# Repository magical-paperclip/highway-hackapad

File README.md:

# highway hackpad
pov: you make your first hardware project and with 12 channel pings in ur personal channel and 8 people helping you build a pcb.
im very proud of my determination and i kept going even when i wanted to give up.

### inspiration
my original inspiration was to build a hackpad that would help me copy and paste, delete, space and using f5 for dev tools as it would help me debug at a faster pace

### Specifications

bom:
4x cherry mx switches (blue)
2x SK6812 mini leds
1x XIAO rp2040
4x blank dsa keycaps (black)

others:
- kmk firmware
- top.step 
- bottom.step

### final product

### info:
the pcb will be secured to the case w double sided tape to prevent it from falling out

schematic            |  pcb         |   case
:-------------------------:|:-------------------------:|:-------------------------:|
    |    |

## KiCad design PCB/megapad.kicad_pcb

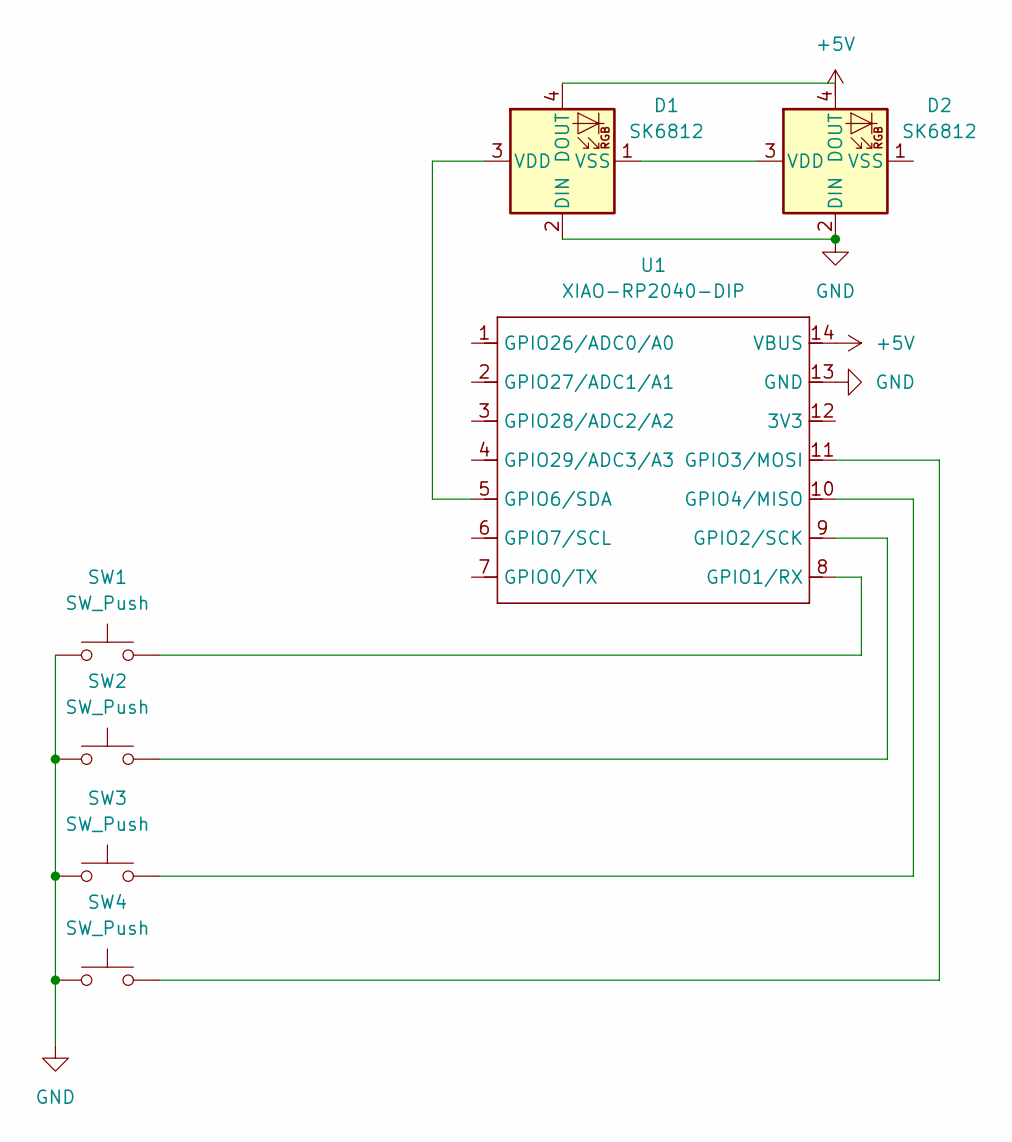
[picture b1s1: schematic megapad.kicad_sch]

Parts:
D1, D2: SK6812; LED_SK6812_PLCC4_5.0x5.0mm_P3.2mm
SW1, SW2, SW3, SW4: SW_Push; SW_Cherry_MX_1.00u_PCB
U1: XIAO-RP2040-DIP

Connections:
+5V: U1.14 (VBUS)
GND: D1.2 (DIN), D2.2 (DIN), SW1.1, SW2.1, SW3.1, SW4.1, U1.13 (GND)
unnamed: D1.4 (DOUT), D2.4 (DOUT)
unnamed: D1.3 (VDD), U1.5 (GPIO6/SDA)
unnamed: D1.1 (VSS), D2.3 (VDD)
unnamed: SW1.2, U1.8 (GPIO1/RX)
unnamed: SW2.2, U1.9 (GPIO2/SCK)
unnamed: SW4.2, U1.11 (GPIO3/MOSI)
unnamed: SW3.2, U1.10 (GPIO4/MISO)

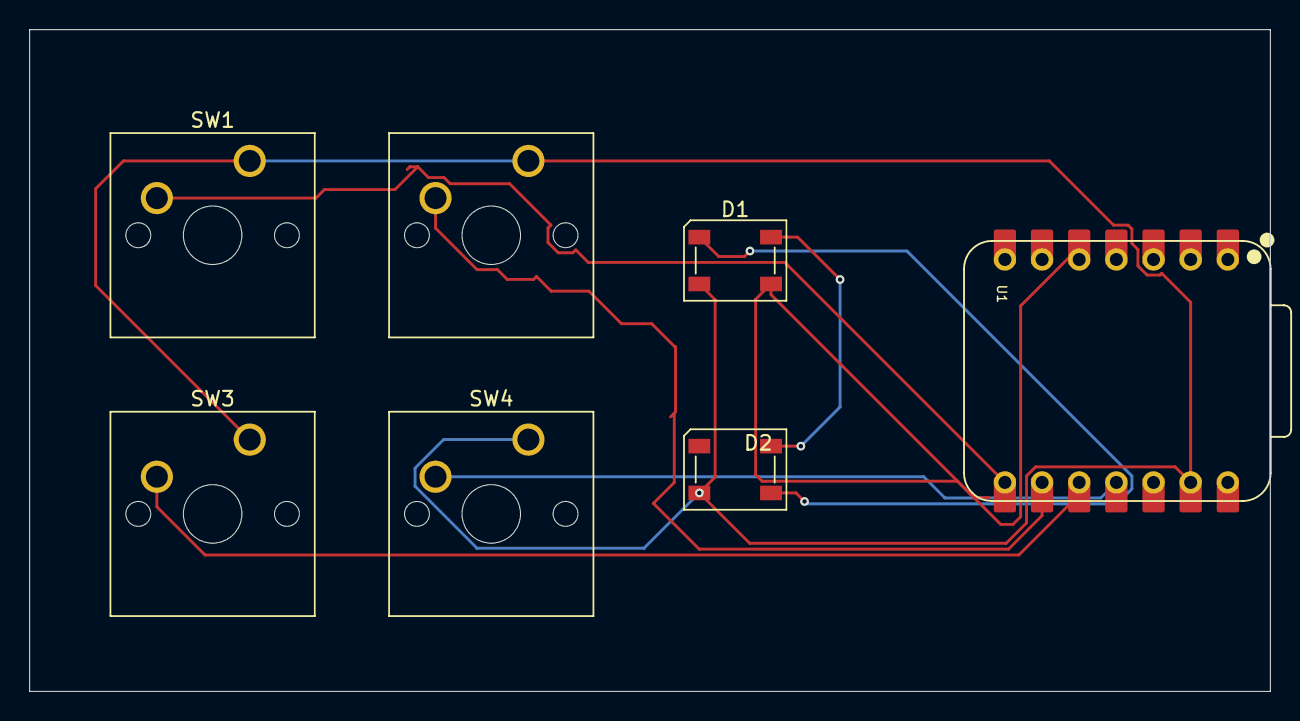
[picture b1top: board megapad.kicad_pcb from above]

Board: 2 copper layers, 84.8 x 45.2 mm, 7 parts (0 on the bottom side), 8 nets.

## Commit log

2025-06-26 project
2025-06-26 Create schematic folder
2025-06-26 Rename megapad.kicad_pro to PCB /megapad.kicad_pro
2025-06-26 Create CAD
2025-06-26 Create case
2025-06-26 made my first cad!! (thanks nick!!)
2025-06-26 Create h
2025-06-26 geibers
2025-06-26 Create h
2025-06-26 *fusion
2025-06-27 FINAL HACKPAD
2025-06-27 Rename final-hackapad.png to final-hackpad.png
2025-06-28 updated case
2025-06-28 case
2025-06-28 Create framework
2025-06-28 Create hi
2025-06-28 firmwarev1 may update later
2025-06-28 NEW SCHEMATIC :yay: !!
2025-06-29 new case
2025-06-29 FINAL CASE
2025-06-29 final product
2025-06-29 Rename image (27).png to best-render.png
